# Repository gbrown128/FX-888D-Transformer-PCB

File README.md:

# FX-888D-Transformer-PCB
A replacement design for the FX-888D mains input transformer PCB.

At the time of writing I have 4 spare boards manufactured. Drop me a message and I'll happily post one out!

Please note I have not verified that this board design passes any specific safety standard. The safety of the design will vary with the quality of PCB substrate used.

This design fits the 120 V unit I have, with a manufacturing date of July 2017. Hakko only seem to offer only one kind of replacement, so I suspect this design will fit all units.

</img>
</img>
</img>

## Replacement Parts

| Part           | Manufacturer | MPN        | Supplier        |
|:---------------|:-------------|:-----------|:----------------|
| Fuse Holder    | Eaton        | HMC-100M   | [Farnell 1845422](https://uk.farnell.com/eaton-bussmann-series/htc-100m/fuse-holder-pcb-250v-5a/dp/2550634) |
| MOV (120V)     | Panasonic    | ERZV05D271 | [Farnell 1845398](https://uk.farnell.com/panasonic-electronic-components/erzv05d271/varistor-5mm-disc-270v/dp/1845398) |
| MOV (120V Alt) | Panasonic    | ERZV07D271 | [Farnell 1845422](https://uk.farnell.com/panasonic/erzv07d271/varistor-7mm-disc-270v/dp/1845422) |

If you have a 240V variant it would be great to add the details about the MOV used. Please submit an issue and I'll update the tables to suit!

I used the larger alternative MOV as the 5 mm disk was out of stock. To my knowledge the larger size just makes for a more robust device.

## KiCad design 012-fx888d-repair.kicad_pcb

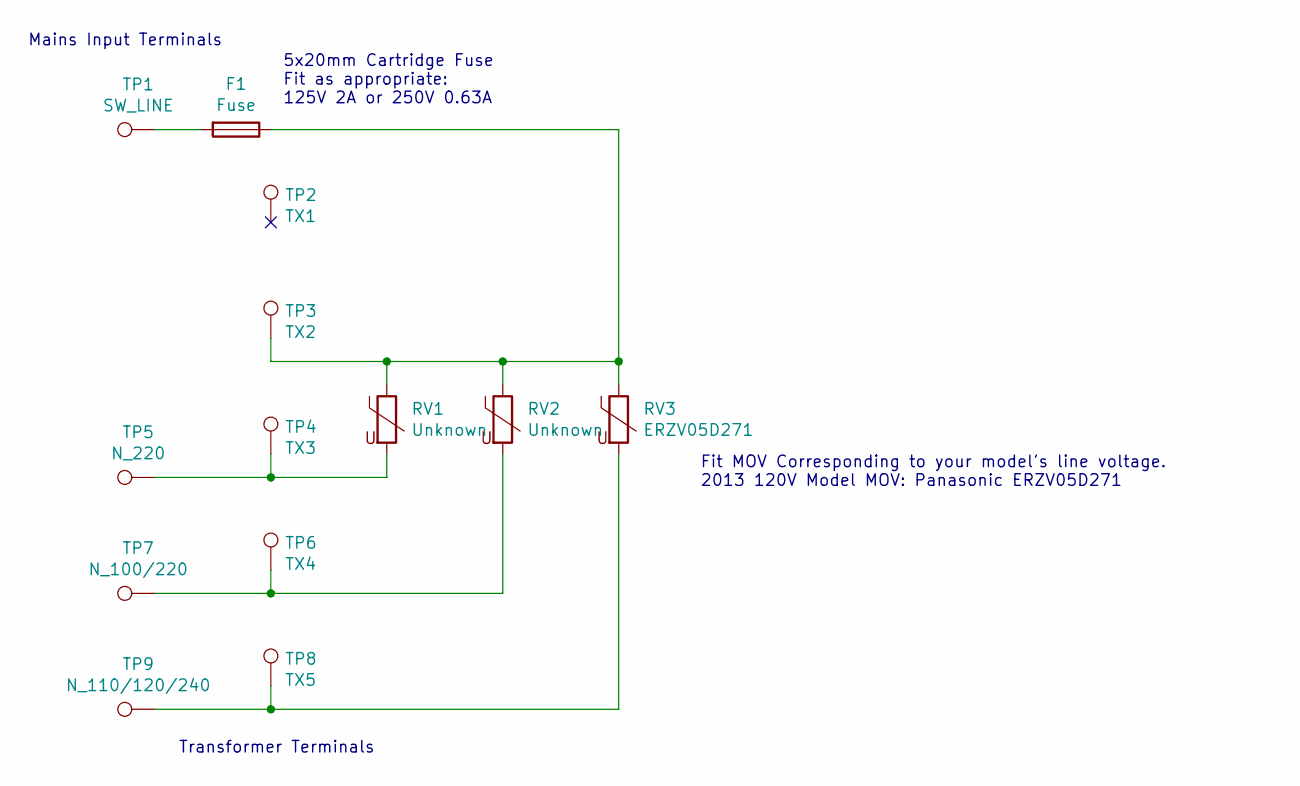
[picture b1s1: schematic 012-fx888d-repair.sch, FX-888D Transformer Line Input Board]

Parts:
F1: Fuse; Fuseholder_Cylinder-5x20mm_Stelvio-Kontek_PTF78_Horizontal_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
RV1, RV2: Unknown; C_Rect_L7.0mm_W4.5mm_P5.00mm
RV3: ERZV05D271; C_Rect_L7.0mm_W4.5mm_P5.00mm
TP1: SW_LINE; TestPoint_Loop_D3.80mm_Drill2.0mm
TP2: TX1; TestPoint_THTPad_D3.0mm_Drill1.5mm
TP3: TX2; TestPoint_THTPad_D3.0mm_Drill1.5mm
TP4: TX3; TestPoint_THTPad_D3.0mm_Drill1.5mm
TP5: N_220; TestPoint_Loop_D3.80mm_Drill2.0mm
TP6: TX4; TestPoint_THTPad_D3.0mm_Drill1.5mm
TP7: N_100/220; TestPoint_Loop_D3.80mm_Drill2.0mm
TP8: TX5; TestPoint_THTPad_D3.0mm_Drill1.5mm
TP9: N_110/120/240; TestPoint_Loop_D3.80mm_Drill2.0mm

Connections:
unnamed: F1.1, RV1.1, RV2.1, RV3.1, TP3.1
unnamed: F1.2, TP1.1
unnamed: RV1.2, TP4.1, TP5.1
unnamed: RV2.2, TP6.1, TP7.1
unnamed: RV3.2, TP8.1, TP9.1

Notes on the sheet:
Fit MOV Corresponding to your model's line voltage. 2013 120V Model MOV: Panasonic ERZV05D271
Mains Input Terminals
Transformer Terminals
5x20mm Cartridge Fuse Fit as appropriate: 125V 2A or 250V 0.63A

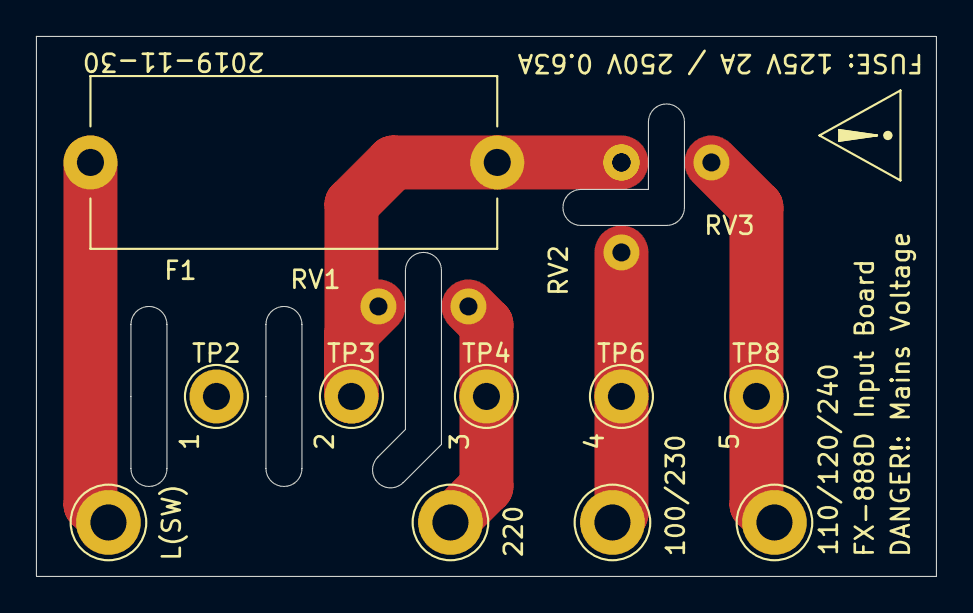
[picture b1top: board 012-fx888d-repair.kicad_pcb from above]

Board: 2 copper layers, 50.0 x 30.0 mm, 13 parts (0 on the bottom side), 5 nets.

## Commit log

2020-01-16 + Add the latest version of the files, brought over from another repo.
2020-01-16 + Add some images to stick in the readme.
2020-01-16 + Add images and more description to the readme.
2020-01-16 * Make web links actually web links not images!
